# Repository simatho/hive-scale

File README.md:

# Bienenstockwaage
Eine *Internet of Things* - Bienenstockwaage.

### Features:
- Zyklisches Messen unterschiedlicher Größen
  - Spannung an der angeschlossenen Messbrücke => Gewicht auf der Waage
  - Temperatur des A/D-Wandlers
  - Temperatur des angeschlossenen 1-Wire-Temperatursensors
- Versenden der Daten per HTTP-GET-Request an eine Datenbank
- Grafische Aufbereitung der Daten im Backend ([Beispiel](http://waage.retsifp.de), auf Grund der laufenden Entwicklung nicht mit echten Daten)
- Open Source Soft- und Hardware!

### Hardware:
- Hauptprozessor, WLAN: Espressif **ESP8266**
- A/D-Wandler: Intersil **ISL26102**
- Tiefsetzer (3V3, 5V0): Linear Technology **LTC3622-23/5**
- Wägezelle: Bosche **H40A**
- Temperatursensor: Maxim **DS18B20**

### Software:
- ESP8266-Firmware: C++ (Greift mit einigen Funktionen auf die [ESP8266-Arduino](https://github.com/esp8266/Arduino/)-Portierung zurück und wird mit dieser Kompiliert)
- Backend: PHP7 (sollte auch mit niedrigeren Versionen funktionieren)
- Darstellung: [nvd3](http://nvd3.org/)
- Datenbank: MySQL

### Hintergrund
Dieses Projekt ist im Rahmen der Vorlesung _Systems Engineering I_ an der [Hochschule für angewandte Wissenschaften Augsburg](https://hs-augsburg.de) entstanden.
In dieser Vorlesung sucht sich eine Gruppe von Studenten ein Projekt, das sie ein Semester lang zu entwickeln versuchen.
Unser Ansatz zielt explizit darauf ab, nachgebaut und weiterentwickelt zu werden.
Da einige Software-Features nicht rechtzeitig fertiggestellt werden konnten, werden diese sukzessive nachgereicht.

### Versionsgeschichte:
#### Für die nächsten Versionen angedachte Features:
- Verwendung der [SPIFFS](https://github.com/pellepl/spiffs)-Bibliothek zum Abspeichern der Konfiguration sowie der Messdaten
- Daten nur alle paar Messzyklen übertragen (und im SPIFFS zwischenspeichern)
- Server kann dem Client eine geänderte Zykluszeit vorgeben

#### Version 0.9.7.2 (03.09.2016)
- Kleinere Verbesserungen am Webinterface
- firmware war nicht kompilierbar, korrigiert

#### Version 0.9.7 (01.09.2016)
- Webinterface: Geräteverwaltung integriert, per Login gesichert
- Anzeigen von Daten wie: Letztes Sendedatum, Firmwareversion
- Erstellen von Geräteklassen
- Einstellen von: Firmwareupdate, Geräteklasse
- Upload von neuen Firmware-Versionen

#### Version 0.9.6 (26.06.2016)
- Erste öffentliche Version
- _firmware/main.cpp_: Instruktionen hinzugefügt, wie die Einstellungs-Datei _settings.h_ beschaffen sein muss. Außerdem Option hinzugefügt, das folgende Feature (z.B. aus Speicherplatzgründen) wieder deaktivieren zu können.
- Alle nötigen Funktionen hinzugefügt, die Firmware über das Internet zu aktualisieren:
- _backend/ota_update.php_: Liefert die Firmware-Datei auf dem Server aus (momentan noch keine Kontrolle, ob Firmware überhaupt aktualisiert werden muss).
- Neue Firmware-Klasse _Updater_: Prüft auf neues Update (ist an dieser Stelle bereits darauf vorbereitet, vom Server die Antwort "nicht aktualisieren" zu bekommen).
- _firmware/main.cpp_: Neue Befehle _autoUpdate_ (Prüft auf neues Update und aktualisiert falls der Server dazu anweist) und _update_ (erzwingt ein Update) hinzugefügt.
- Mehrere kleinere Änderungen und Verbesserungen, Refactoring

#### Version 0.9 (21.06.2016, Präsentationsstand HSA)
- An der HSA präsentierte und so auch zur Bewertung abgegebene Version

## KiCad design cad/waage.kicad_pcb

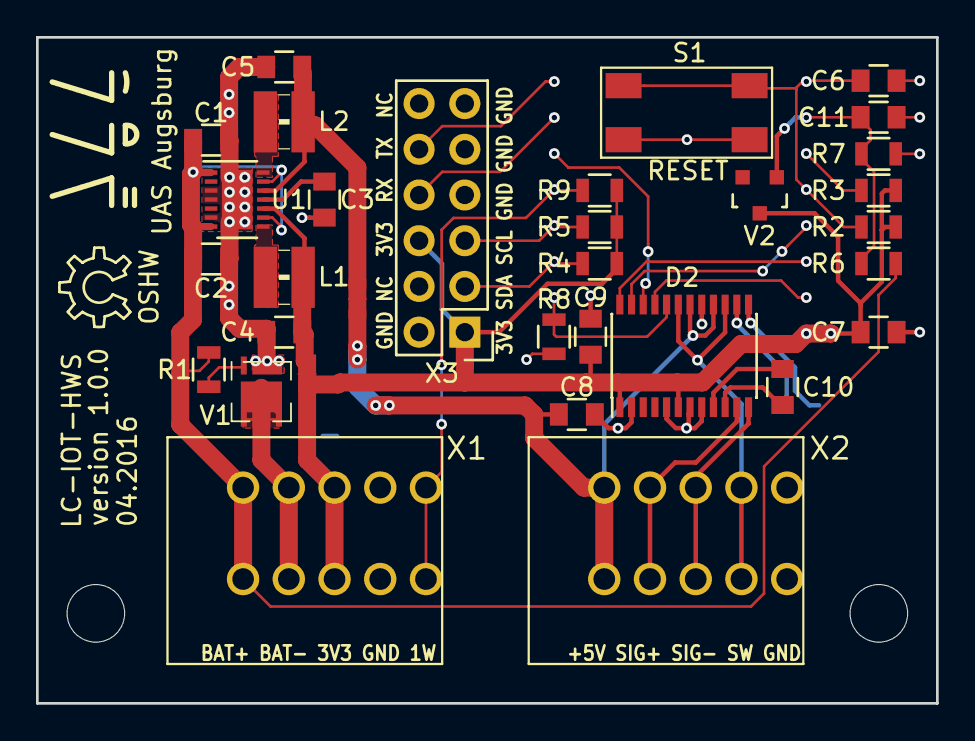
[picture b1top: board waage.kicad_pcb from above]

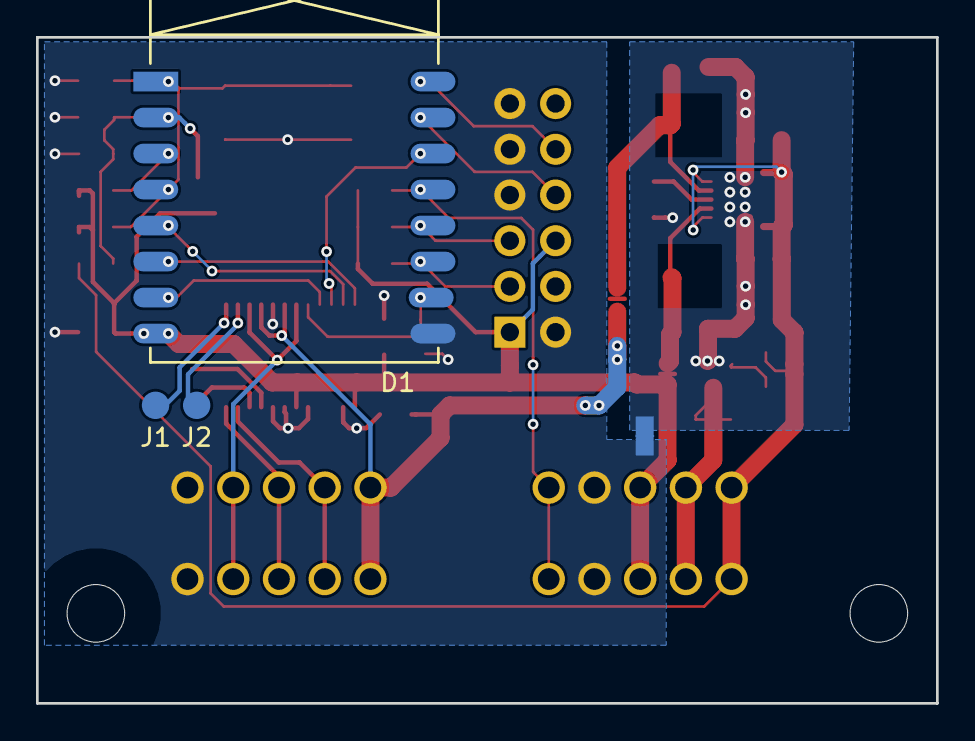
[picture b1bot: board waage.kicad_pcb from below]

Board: 2 copper layers, 50.0 x 37.0 mm, 43 parts (4 on the bottom side), 32 nets.

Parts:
C1, C2: 10u; C_0805
C3, C8, C9: 1u; C_0805
C4, C5: 22u; C_0805
C6, C7, C10, C11: 100n; C_0805
D1: s:ESP-07v2; ESP-07v2
D2: s:ISL26102; TSSOP-24_4.4x7.8mm_Pitch0.65mm
DRL1, DRL2: HOLE; HOLE_M3
FLG1: SYMBOL; FH-Logo
FLG2: SYMBOL; OSHW-LOGO-M
FLG3: version 1.0.0; TEXT
FLG4: 04.2016; TEXT
FLG5: LC-IOT-HWS; TEXT
J1, J2: TST; Measurement_Point_Round-SMD-Pad_Small
L1: 6.8u; WE-MAPI_3020
L2: 3.3u; WE-MAPI_3020
N1, N2, N3: NET_TIE; NET_TIE_1mm
R1, R7: 68k; R_0805
R2, R3, R4, R5, R8, R9: 10k; R_0805
R6: 1M; R_0805
S1: RESET; WE-430181038816
U1: LTC3622; DFN-14-1EP_3x4mm_Pitch0.5mm
V1: Q_NMOS_DSG; TSDSON
V2: BAT54C; SOT-23
X1: BAT+1WIRE; WE-691403900005B
X2: SENSOR; WE-691403900005B
X3: FTDI I²C; Pin_Header_Straight_2x06

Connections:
+3V3: C7.1, C9.2, D1.8, D2.1, D2.6, N2.1, R2.2, R3.2, R4.1, R5.1, R9.1, V2.3, X1.3, X3.1, X3.6
+5V: C8.2, D2.16, D2.18, N3.1, X2.5
+12V: C1.1, C2.1, R1.2, R6.2, U1.1, U1.7, U1.9, U1.13, X1.5
/1Wire: D1.13, R9.2, X1.1
/BAT_MON: C11.2, D1.2, R6.1, R7.2, V2.1
/EXC-: D2.15, D2.19, X2.2
/MISO: D1.6, D2.24
/MOSI: D1.7, D2.21
/N_CS: D1.10, D2.20, R8.1
/N_PWDN: D1.14, D2.22
/N_RST: C6.2, D1.1, D1.4, R2.1, S1.3, S1.4
/RX: D1.15, X3.8
/SCL: D1.12, R5.2, X3.5
/SCLK: D1.5, D2.23
/SDA: D1.11, R4.2, X3.3
/Sig+: D2.11, X2.4
/Sig-: D2.12, X2.3
/TX: D1.16, X3.10
/VCC1: C5.1, L2.2, N3.2, U1.12
/VCC2: C4.1, L1.1, N2.2, U1.10
GND: C6.1, C7.2, C8.1, C9.1, C11.1, D1.9, D2.2, D2.5, D2.7, D2.8, D2.17, N1.2, R7.1, R8.2, S1.1, S1.2, X1.2, X2.1, X3.2, X3.7, X3.9, X3.11
GNDPWR: C1.2, C2.2, C3.2, C4.2, C5.2, N1.1, U1.3, U1.4, U1.6, U1.15, V1.2
GNDREF: V1.1, X1.4
unnamed: C3.1, U1.11
unnamed: C10.1, D2.9
unnamed: C10.2, D2.10
unnamed: D1.3, R3.1
unnamed: D2.13, J1.1
unnamed: D2.14, J2.1
unnamed: L1.2, U1.8
unnamed: L2.1, U1.14
unnamed: R1.1, V1.3

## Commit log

2016-06-26 Erstes öffentliches Release
2016-06-26 Nachtrag
2016-09-01 * Version 0.9.7 * Geräteverwaltung hinzugefügt * Kleinere Verbesserungen
2016-09-03 * Fix kompilier-Fehler firmware * Kleine Verbesserungen im Webinterface * Kleinere Bugfixes bei der Updateverwaltung
